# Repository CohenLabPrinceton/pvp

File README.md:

# The People's Ventilator Project

All information is in the documentation:
https://pvp.readthedocs.io/

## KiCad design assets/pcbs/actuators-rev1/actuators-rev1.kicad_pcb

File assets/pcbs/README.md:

# Content of pcbs
This folder contains PCB design files for the PVP1. There are two boards: one for the Actuators and one for the Sensors. They connect to the the Raspberry Pi 4 via 40-pin stackable headers. Uploaded as KiCad project files except where noted.

# Actuator Board (actuators-rev2)
	- Interfaces the Raspberry Pi to the inspiratory and expiratory valves through an array of solenoid drivers (ULN2003A Darlington transistor array)
	- Revision history:
		- rev2 (6/14/2020): Present version. Removed one screw terminal and the adjustable headers. Four of the darlington pairs are tied together to drive the expiratory valve, and three are tied together to drive the proportional valve. These connections are now permanent traces on the PCB.
		- rev1 (5/13/2020): Initial version. Three screw terminals intended to connect to valves. Included extra jumpers J4, J8, J9, and J10 designed to tie together Darlington pairs for felxibility if more current was needed to drive a particular valve.
		
# Sensor Board (pressure-rev2)
	- Interfaces four analog output sensors with the Raspberry Pi via I^2C commands to a 12-bit 4-channel ADC (Adafruit ADS1015)
	- Revision history:
		- rev2 (6/14/2020): Present version. Added a third auxiliary pressure sensor, and revised analog front-end for oxygen sensor. Added a TL7660 charge pump to provide a dual-sided supply to the INA126 instrumentation amplifier. Connections for I2C resistors removed.
		- rev1 (4/27/2020): Initial version. Shared as Gerber production files. Connections included for two pressure sensors, oxygen sensor, and flow sensor.

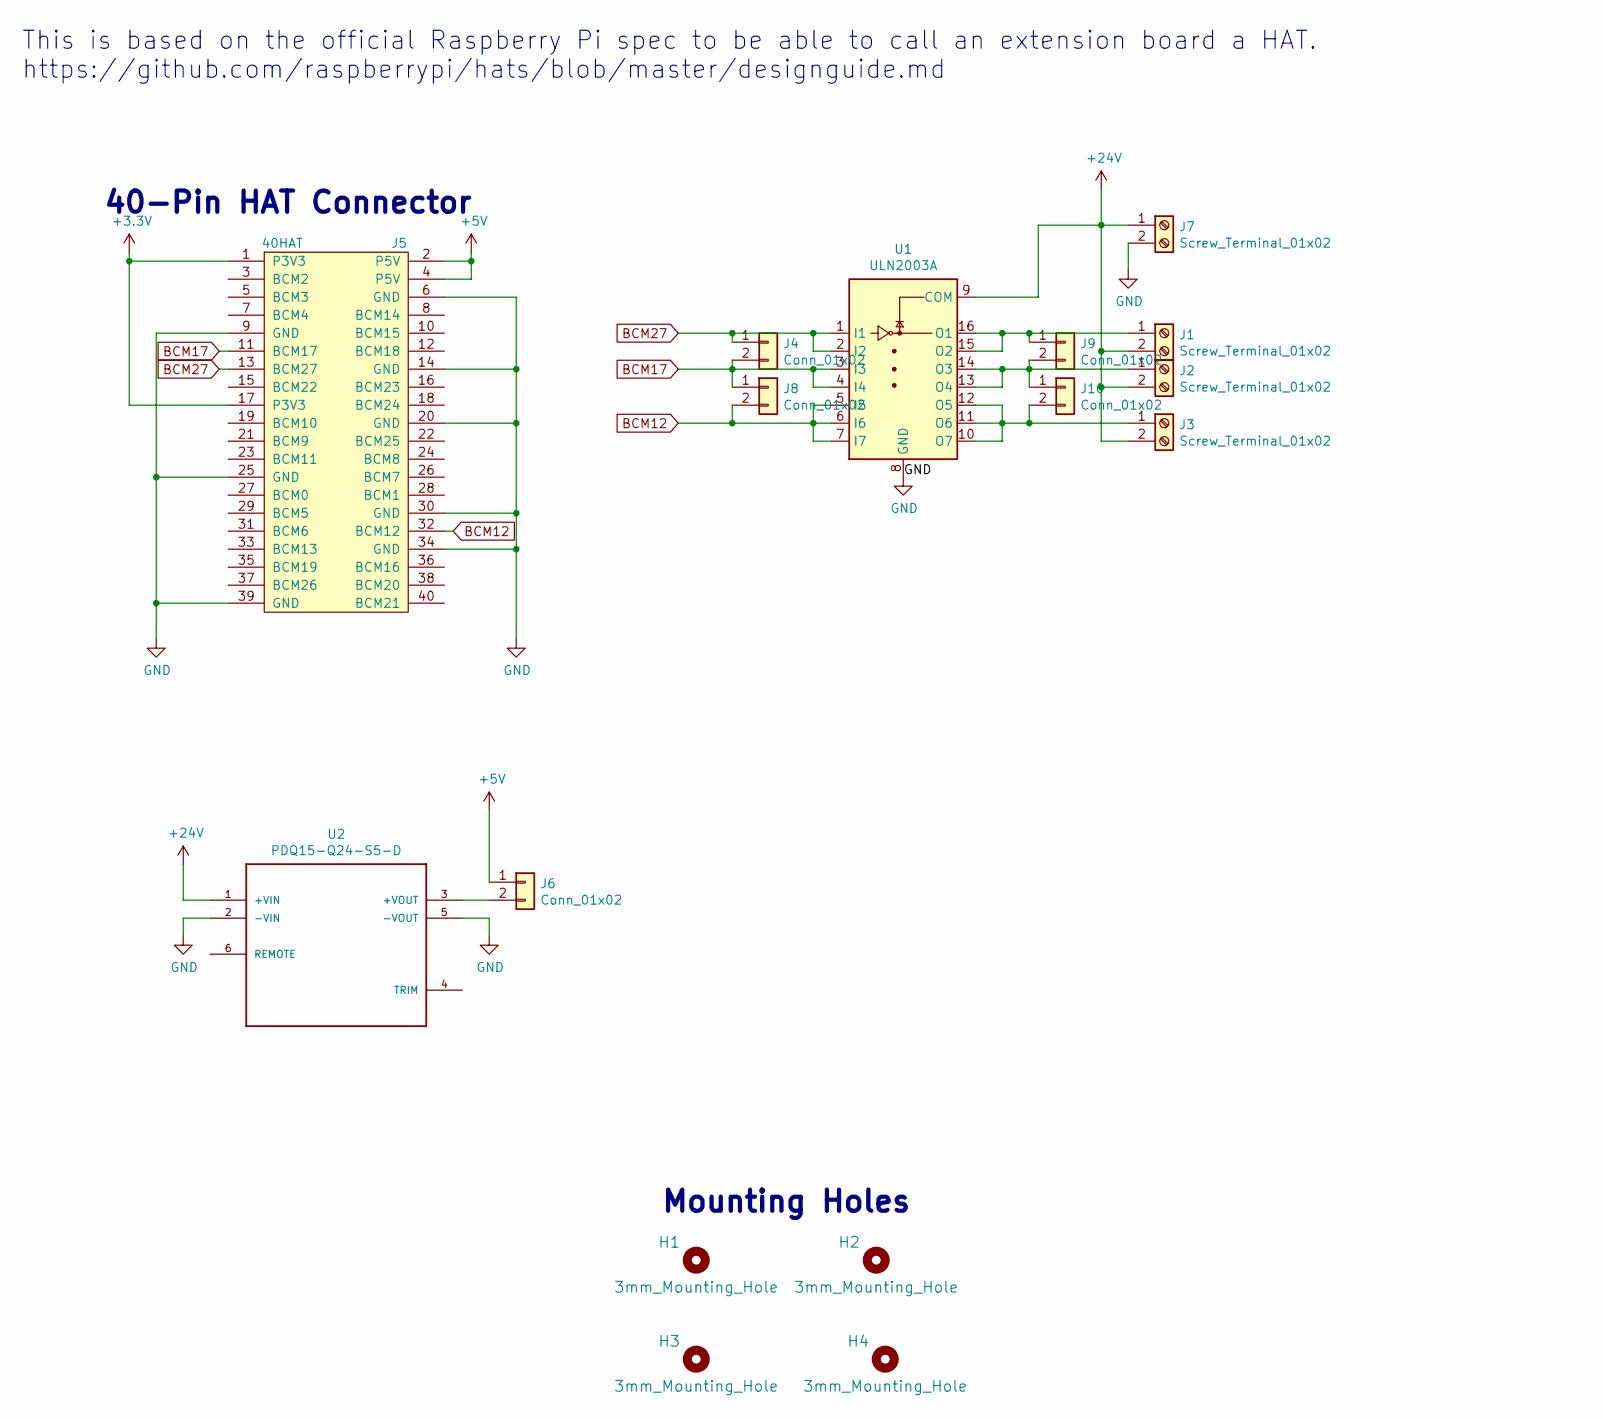
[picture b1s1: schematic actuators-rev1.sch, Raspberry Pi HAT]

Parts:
H1, H2, H3, H4: 3mm_Mounting_Hole; NPTH_3mm_ID
J1, J2, J3, J7: Screw_Terminal_01x02; TerminalBlock_Altech_AK300-2_P5.00mm
J4, J6, J8, J9, J10: Conn_01x02; PinHeader_1x02_P2.54mm_Vertical
J5: 40HAT; PinSocket_2x20_P2.54mm_Vertical
U1: ULN2003A; DIP-16_W7.62mm
U2: PDQ15-Q24-S5-D; CONV_PDQ15-Q24-S5-D

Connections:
+3V3: J5.1 (P3V3), J5.17 (P3V3)
+5V: J5.2 (P5V), J5.4 (P5V), J6.1
+24V: J1.2, J2.2, J3.2, J7.1, U1.9 (COM), U2.1 (+VIN)
BCM12: J5.32 (BCM12), J8.2, U1.5 (I5), U1.6 (I6), U1.7 (I7)
BCM17: J4.2, J5.11 (BCM17), J8.1, U1.3 (I3), U1.4 (I4)
BCM27: J4.1, J5.13 (BCM27), U1.1 (I1), U1.2 (I2)
GND: J5.6 (GND), J5.9 (GND), J5.14 (GND), J5.20 (GND), J5.25 (GND), J5.30 (GND), J5.34 (GND), J5.39 (GND), J7.2, U1.8 (GND), U2.2 (-VIN), U2.5 (-VOUT)
unnamed: J1.1, J9.1, U1.15 (O2), U1.16 (O1)
unnamed: J6.2, U2.3 (+VOUT)
unnamed: J2.1, J9.2, J10.1, U1.13 (O4), U1.14 (O3)
unnamed: J3.1, J10.2, U1.10 (O7), U1.11 (O6), U1.12 (O5)

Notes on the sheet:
Mounting Holes
40-Pin HAT Connector
This is based on the official Raspberry Pi spec to be able to call an extension board a HAT. https://github.com/raspberrypi/hats/blob/master/designguide.md

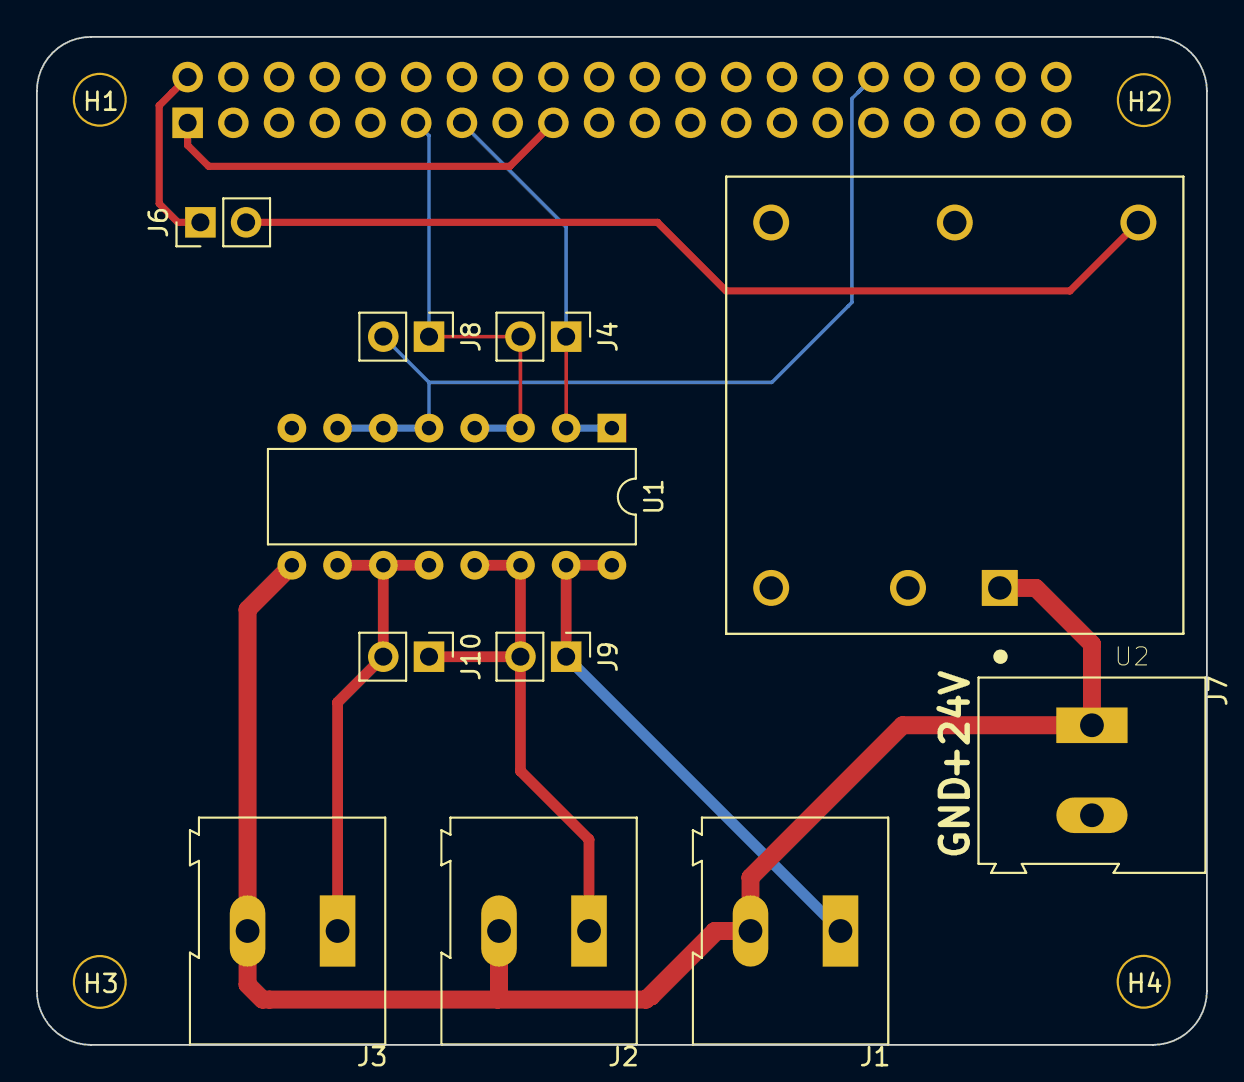
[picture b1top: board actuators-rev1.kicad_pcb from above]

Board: 4 copper layers, 65.0 x 56.0 mm, 16 parts (1 on the bottom side), 11 nets.

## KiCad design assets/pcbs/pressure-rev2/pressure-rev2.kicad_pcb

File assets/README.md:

# Content of assets
This folder contains all technical drawings for PVP1, the drawings for parts to be 3D-printed, and printed circuit boards.
In addition, to aid discoverability, we have generated a standardized Open Know How Manifest (OKH-manifest): [`okh-manifest.yml`](okh-manifest.yml). This follows the Open Know-How Manifest Specification Version 1.0. Finally, the file `PVP1 Assembly Instructions.pdf` contains detailed step-by-step assembly instructions.
The following folders exist:

# cad
Contains a 3D-printable PEEP valve, as single-use PEEP valves can be subject to supply chain limitations. 

# DXFs
Contains drawings for laser cutting of the chassis.

# PCBS
This folder contains all of the electrical design files for our custom PCBs. 

# SOLIDWORKS
This folder contains CAD drawings of PVP1, more specifically:
1. Technical drawings of the PVP1 Mk3, in Solidworks. This is the device documented in the article, and featured in the detailed assembly instructions. This final version of PVP1 removed non-critical components, such as the humidifier and Gauges, and introduced more standardized parts.
1. The previous version of the device, Mk2, using few standardized components, and featuring a humidifier. Notice the `CPAP_BIPAP_HEATER_HUMIDIFIER_ASSY`.
1. Mk1, the first version of PVP1. This served as an early sketch about what to include in the design

# STLs
This folder contains all of our 3D printed components/fixtures that are not included in our Bill-of-Materials.

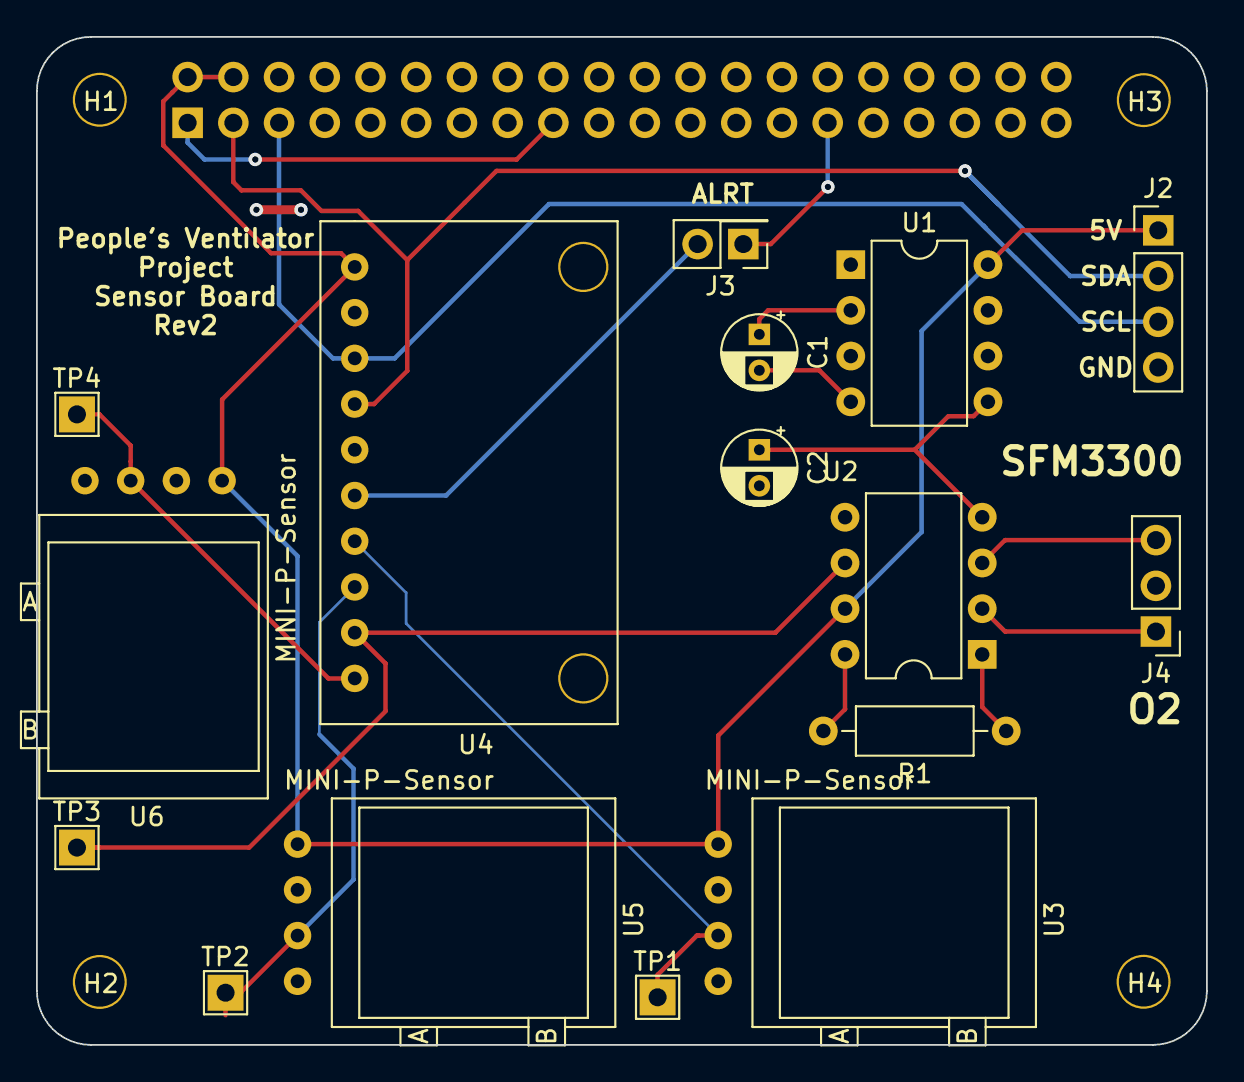
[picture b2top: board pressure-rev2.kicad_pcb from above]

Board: 2 copper layers, 65.0 x 56.0 mm, 21 parts (1 on the bottom side), 18 nets.

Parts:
C1, C2: CP1; CP_Radial_D4.0mm_P2.00mm
H1, H2, H3, H4: 3mm_Mounting_Hole; NPTH_3mm_ID
J1: 40HAT; PinSocket_2x20_P2.54mm_Vertical
J2: Conn_01x04; PinHeader_1x04_P2.54mm_Vertical
J3: Conn_02x01; PinHeader_2x01_P2.54mm_Vertical
J4: Conn_01x03; PinHeader_1x03_P2.54mm_Vertical
R1: R; R_Axial_DIN0207_L6.3mm_D2.5mm_P10.16mm_Horizontal
TP1, TP2, TP3, TP4: TestPoint; TestPoint_THTPad_2.0x2.0mm_Drill1.0mm
U1: TL7660; DIP-8_W7.62mm
U2: INA126; DIP-8_W7.62mm
U3, U5, U6: MINI-P-Sensor; MINI-P-Sensor-Horizontal
U4: Adafruit_ADS1115

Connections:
+3V3: J1.1, J1.17
+5V: J1.2, J1.4, J2.1, U1.8, U2.7, U3.1, U4.1, U5.1, U6.1
/J_ALRT: J1.29, J3.1
/SCL: J1.5, J2.3, U4.3
/SDA: J1.3, J2.2, U4.4
GND: C2.2, J1.6, J1.9, J1.14, J1.20, J1.25, J1.30, J1.34, J1.39, J2.4, J4.2, U1.3, U2.5, U3.2, U4.2, U4.5, U5.2, U6.2
unnamed: C1.1, U1.2
unnamed: C1.2, U1.4
unnamed: C2.1, U1.5, U2.4
unnamed: J3.2, U4.6
unnamed: J4.1, U2.2
unnamed: J4.3, U2.3
unnamed: R1.1, U2.1
unnamed: R1.2, U2.8
unnamed: TP1.1, U3.3, U4.7
unnamed: TP2.1, U4.8, U5.3
unnamed: TP3.1, U2.6, U4.9
unnamed: TP4.1, U4.10, U6.3

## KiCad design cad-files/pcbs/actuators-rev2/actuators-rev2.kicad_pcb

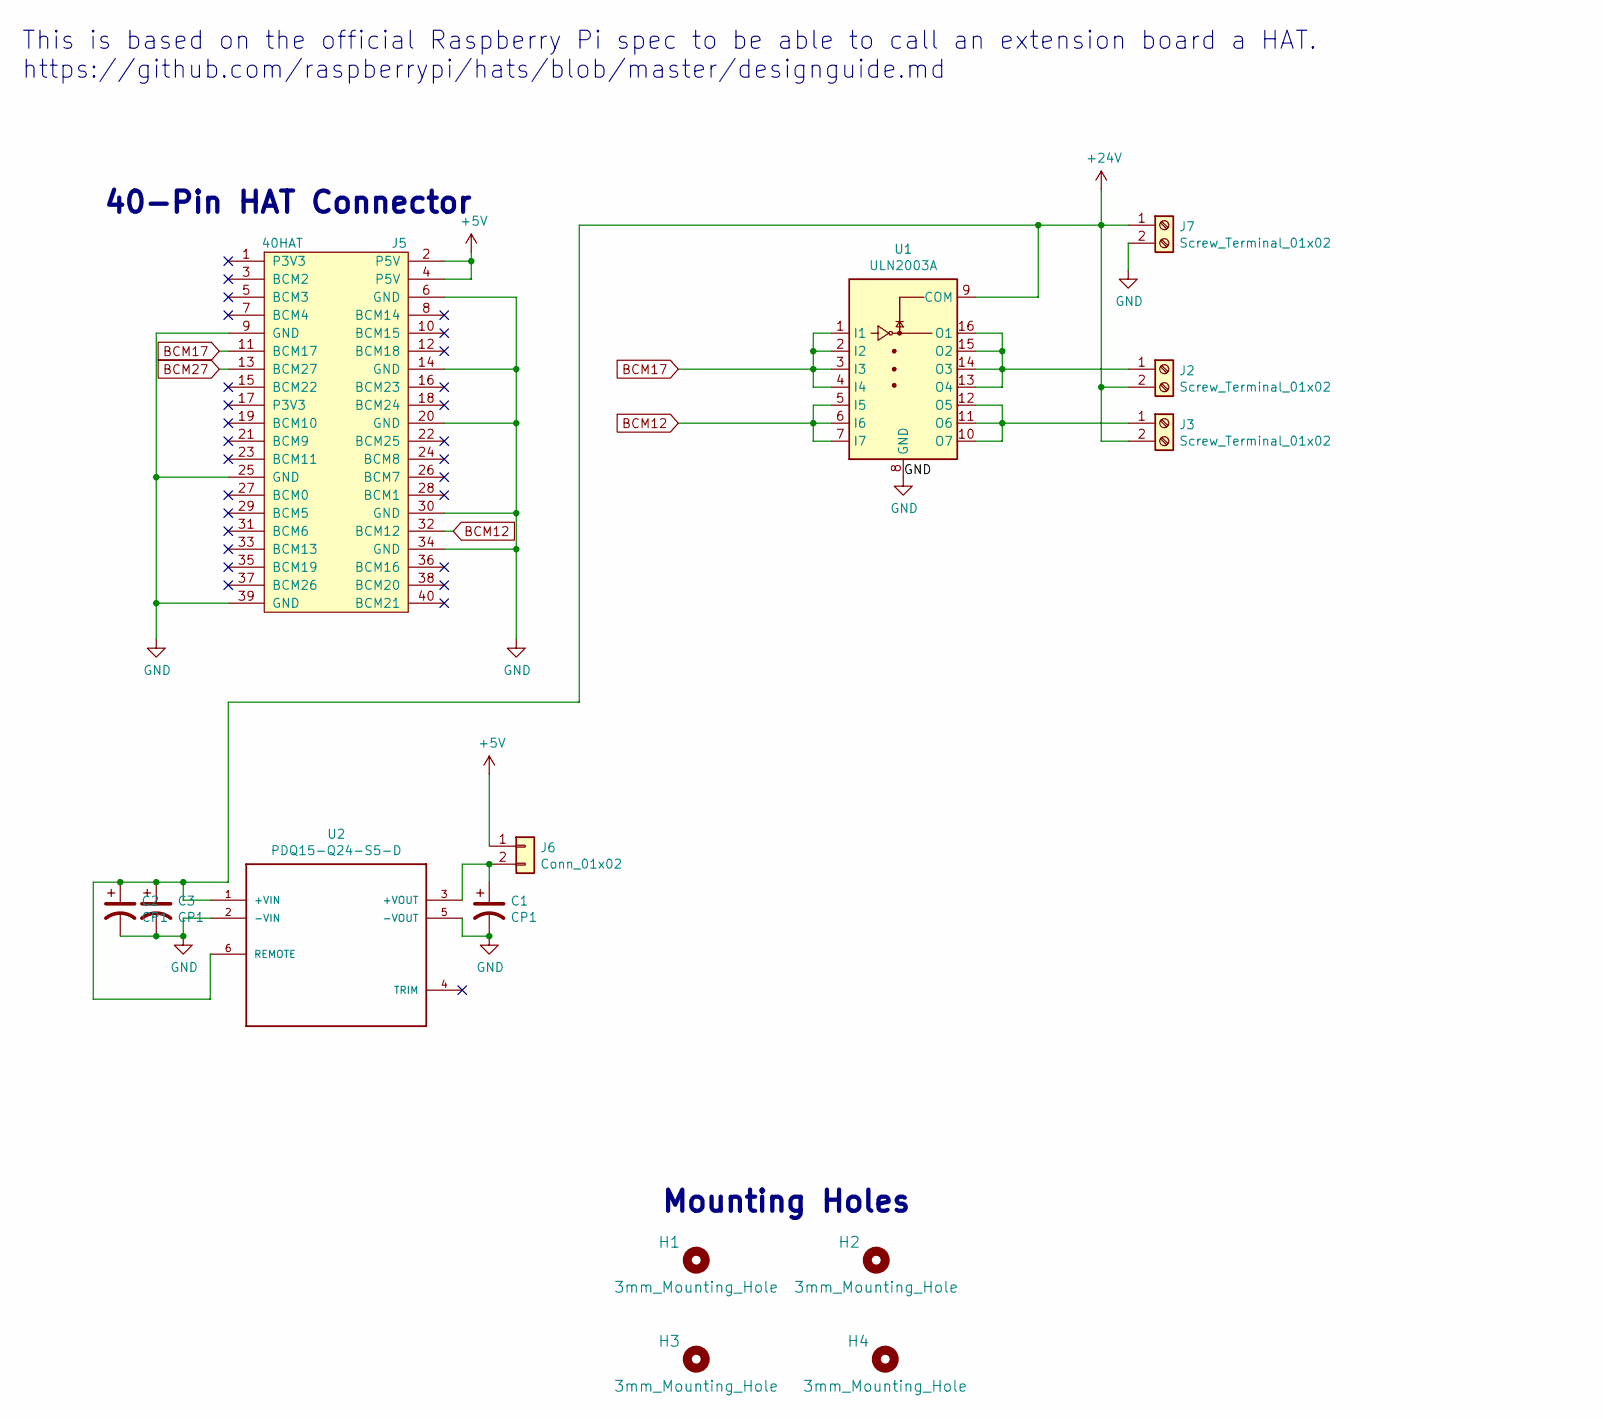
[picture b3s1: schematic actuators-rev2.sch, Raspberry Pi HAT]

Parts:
C1: CP1; CP_Radial_D5.0mm_P2.00mm
C2, C3: CP1; CP_Radial_D5.0mm_P2.50mm
H1, H2, H3, H4: 3mm_Mounting_Hole; NPTH_3mm_ID
J2, J3, J7: Screw_Terminal_01x02; TerminalBlock_Altech_AK300-2_P5.00mm
J5: 40HAT; PinSocket_2x20_P2.54mm_Vertical
J6: Conn_01x02; PinHeader_1x02_P2.54mm_Vertical
U1: ULN2003A; DIP-16_W7.62mm
U2: PDQ15-Q24-S5-D; CONV_PDQ15-Q24-S5-D

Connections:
+5V: J5.2 (P5V), J5.4 (P5V), J6.1
+24V: C2.1, C3.1, J2.2, J3.2, J7.1, U1.9 (COM), U2.1 (+VIN), U2.6 (REMOTE)
BCM12: J5.32 (BCM12), U1.5 (I5), U1.6 (I6), U1.7 (I7)
BCM17: J5.11 (BCM17), U1.1 (I1), U1.2 (I2), U1.3 (I3), U1.4 (I4)
BCM27: J5.13 (BCM27)
GND: C1.2, C2.2, C3.2, J5.6 (GND), J5.9 (GND), J5.14 (GND), J5.20 (GND), J5.25 (GND), J5.30 (GND), J5.34 (GND), J5.39 (GND), J7.2, U1.8 (GND), U2.2 (-VIN), U2.5 (-VOUT)
unnamed: C1.1, J6.2, U2.3 (+VOUT)
unnamed: J2.1, U1.13 (O4), U1.14 (O3), U1.15 (O2), U1.16 (O1)
unnamed: J3.1, U1.10 (O7), U1.11 (O6), U1.12 (O5)

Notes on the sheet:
Mounting Holes
40-Pin HAT Connector
This is based on the official Raspberry Pi spec to be able to call an extension board a HAT. https://github.com/raspberrypi/hats/blob/master/designguide.md

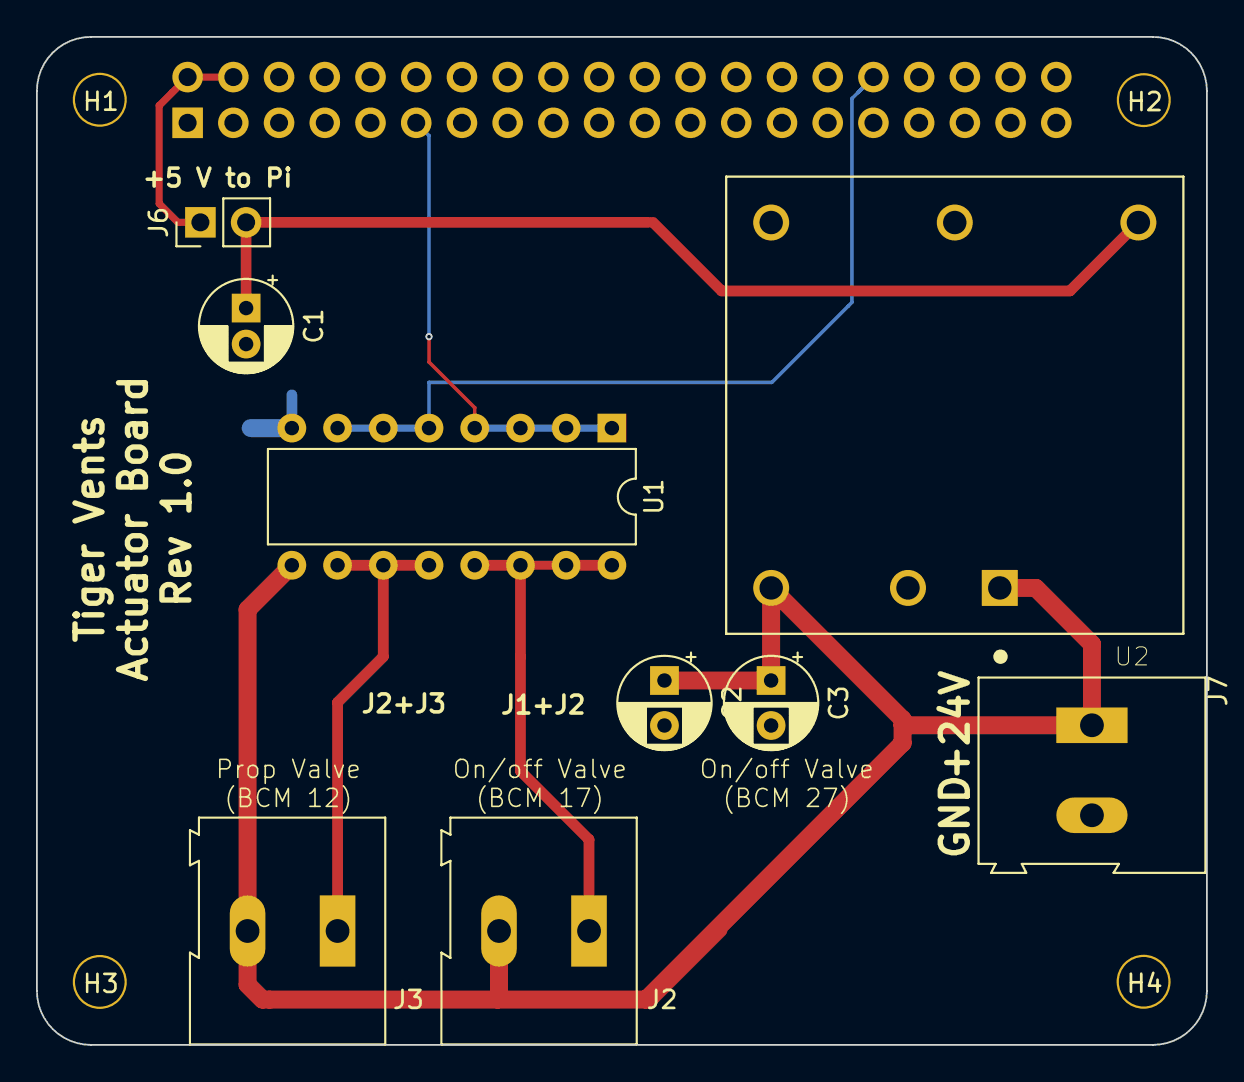
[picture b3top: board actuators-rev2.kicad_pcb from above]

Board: 4 copper layers, 65.0 x 56.0 mm, 14 parts (1 on the bottom side), 8 nets.

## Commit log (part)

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2020-08-11 Update test_timeoutdecorator.py
    This should be consistent as 5*dt
2020-08-11 ignoring build and dist
2020-08-12 audio system using QSoundEffect for buffering
2020-08-12 maybe docker wasnt the right idea
2020-08-12 refactoring vent to pvp
    and updating some missing entries in the docs and rebuilding the docs
2020-08-12 moving some external files to a subdirectory in pvp for packaging
2020-08-12 working on tests -- just wanna look at coverage report to see what's missing
2020-08-12 working on some code coverage of main gui widget
2020-08-12 coordinator doesn't kill controller on stop...
2020-08-12 killing dead code
    - RIP the ideal waveform plot it was a good idea ahead of its time.
    - RIP the rangeslider which should be built into Qt but we had to do hand to hand fucking pixelwise drawing for like a week to make. it still was sorta shitty so good riddance
    - Welcome back to life tests for doubleslider
2020-08-12 always do coveralls!!
2020-08-12 Checking in GUI tests and some healthy code cleanup (#135)
    * working on tests -- just wanna look at coverage report to see what's missing
    * coveralls always!
    * working on some code coverage of main gui widget
    * coordinator doesn't kill controller on stop...
    * we got too soft on em, actually killing when closing gui
    also explicitly testing VTE since its just a lil different as it doesnt have a corresponding control in the controller
2020-08-13 little touchups for screenshot
    fix misnamed valve reset function in main
2020-08-14 updating badge urls
2020-08-14 hook up mute button
    - add FIO2 to available plots
    - controller resets _last_update time when starting so don't reset cycle immediately on start
    - version indicator to control panel
    - labels off of plot controls
    - made limit labels clearer in plots
    - added logo to gui
2020-08-14 change colors of display objects when they cause alarms
    - add 'cause' field to alarm objects
    - add 'depends' and 'value_names' to alarm rules to make it easier for them to be queried
2020-08-14 keep color coding consistent through state changes update screenshot to use color coding
2020-08-14 updating link to docs
2020-08-14 refactoring into assets directory
2020-08-15 prevent erroring
2020-08-15 quieter pylint
2020-08-15 actually including iamges
2020-08-15 test flexbox, add placeholders, basic toctree shifting
2020-08-15 favicon remove image logo
2020-08-15 on second thought that was a bad organization
2020-08-15 correct image url
2020-08-15 header text, icon size,
2020-08-15 hideen homepage toctrees
2020-08-15 doubt this toctree works
2020-08-15 actually add the depends
2020-08-15 git repo
2020-08-15 actually in a directive
2020-08-15 relative path?
2020-08-15 header margins
2020-08-15 min_width
2020-08-15 sizing and wrapping
2020-08-15 whoops forgot how sass worked lol
2020-08-15 styling subelements
2020-08-15 wait wat
2020-08-15 idk just smag it
2020-08-15 has the output been wrong this whole time?
2020-08-15 basic software copy
2020-08-15 css grid
2020-08-16 fixing links
2020-08-16 testing bolded links, adding contributing stub
2020-08-16 reordering Software Toctree
2020-08-16 software overview, clickable this time
2020-08-16 include libpulse-dev
2020-08-16 mock import
2020-08-16 expanding gui to multiple pages refactoring Vent_GUI to PVP_Gui
2020-08-16 splitting widgets out to different pages, adding gui overview
2020-08-16 bigger class size name
2020-08-16 initial gui docs
2020-08-16 unnest toctree
2020-08-16 take out unnecessary header
2020-08-16 good ole fashioned way of collapsing
2020-08-16 docs for main gui widget software overview
2020-08-16 do class level docstrings render better?
2020-08-16 Pull and squash initial docs styling and GUI documentation (#138)
    * test pylint
    * prevent erroring
    * quieter pylint
    * test images, include summary report
    * actually including iamges
    * test flexbox, add placeholders, basic toctree shifting
2020-08-16 added basic copy from paper to intro
2020-08-16 added electronics diagram
2020-08-16 added some writeup of pvp electronics/hardware
2020-08-16 common module overview
2020-08-16 Docstrings for values.py
2020-08-17 splitting alarm into multiple files
2020-08-17 actually adding to toctree
2020-08-17 test syntax highlighting?
2020-08-17 finding the right objects maybe?
2020-08-17 moving example to alarm rule page
    adding docstring to alarm definition
2020-08-17 toc in the main page
2020-08-17 correct titles in alarm toc
2020-08-17 link to alarm rule source
2020-08-17 alarm manager documentation
2020-08-17 condition documentation
2020-08-17 importing correctly
2020-08-17 prefs documentation
2020-08-17 messages docs
2020-08-17 test order of class and init docstrings
2020-08-17 unit conversions docs
2020-08-18 alarm bar documentation
2020-08-18 source link color
2020-08-18 control panel docs
2020-08-18 plot docs
2020-08-18 statement on components
2020-08-18 Jonny finished with docs (#139)
    whup whup
    - narrative documentation for software overview, all gui modules, all alarm modules, common.values , common.message (except for stuff manuel needs ta do), common.loggers (except for stuff manuel need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
    - API documentation, docstrings for every method, user-facing attribute, function and constant in all the above. Only exception is gui.widgets.components which are p self explanatory
    - Figures for software overview, gui overview, gui screenshot
    - cleaned up dead/obsolete code with no uses in all the above
    * common module overview
2020-08-18 testing dependencies
2020-08-18 alarm severity condition
2020-08-18 unit conversion tests lol
2020-08-18 sorta weak conversion test but it is specific enough that it works for now
2020-08-18 alarm bar test
2020-08-18 resetting alarm manager state
2020-08-18 dont include the screenshot function...
2020-08-18 shorten delays
2020-08-18 Uploading STL files 8/18/20
2020-08-18 test breath detection
2020-08-18 test timer in ms
2020-08-18 correct message in confirm unsafe
2020-08-18 test unit conversions in run
2020-08-18 stop the timers
2020-08-18 test plot toggling
2020-08-19 correct unit conversions, and unit conversions in control tests
2020-08-19 fix heartbeat call to setText
2020-08-19 oh and updating the unit conversion test
    doing a round instead of int which i assume takes floor
2020-08-19 mercifully shorten testing time by skipping pointless tests
2020-08-19 testing keyboard actions on editable label separately from general control testing
2020-08-19 Gui tests (#140)
    Tests for all my shit.
    also
    - some improvements on adding conditions together (copying the object rather than modifying in place)
    - adding reset to condition addition
    - fixing a disastrously incorrect unit conversion
    - get_breath_detection method for controller since we decided against having a generalized messaging infrastructure and this is the consequence!
2020-08-19 generated gerber files
2020-08-19 more pcb docs
2020-08-19 added sensor pcb bom
2020-08-19 list edits
2020-08-19 try bom path
2020-08-19 upres schematics
2020-08-19 Update hardware_electronics.rst
    spacing for figure captions
2020-08-19 Update hardware_electronics.rst
    spacing between toctree option block
2020-08-19 Update hardware_electronics.rst
    maybe relative links work?
2020-08-19 Update hardware_electronics.rst
    trying two ways -- url and with the full relative path (from conf.py)
2020-08-19 update sensor bom
2020-08-19 enum lists?
2020-08-20 sizing
2020-08-20 edit powerio bom
2020-08-20 figwidth
2020-08-20 remove toctree
2020-08-21 terminate a tag correctly
2020-08-21 cleaning up some hardware docs
2020-08-24 fix cap error in bom
2020-08-24 cleaning up docs
2020-08-24 update schematic img and file for sensor board
2020-08-24 lots of hardware docs reconfiguring
2020-08-24 hardware docs reconfiguration
2020-08-24 add a toc
2020-08-24 tocs, tocs everywhere
2020-08-24 organizing the tocs
2020-08-24 added performance page
2020-08-24 trying to fix the toc
2020-08-24 add pcb project links
2020-08-24 get the assembly on track
2020-08-25 add figures and performance writeup
2020-08-25 update performance
2020-08-26 performance update
2020-08-26 few text updates
2020-08-26 making controller more robust
2020-09-03 local changes for the long run
2020-09-03 removed default PIP in HAPA, as discussed
2020-09-04 updated sensor pcb schematic to reflect pressure/airflow sensor swap
2020-09-04 New tests for the logger
2020-09-05 bug
    no pylab needed in the tests
2020-09-05 few more outputs, and a MockHAL
    ...if HAL doesn't load. Fixed timeout 5 seconds
2020-09-05 too many outputs for travis to handle :-)
2020-09-06 try without these two tests
2020-09-06 one more test
2020-09-06 come on travis; you can do it
2020-09-06 streamlined hal test
2020-09-06 more cleanup
2020-09-06 nan pressure test
2020-09-06 fix travis?
2020-09-06 new nantest
2020-09-06 update for travis
2020-09-06 getting rid of unused code
2020-09-06 removed tre/except and replaced with ifs
2020-09-06 whoopsi
2020-09-07 Cover HAPA and TECHA
    and ignore the OS tests for running out of space
2020-09-07 final check: the no-alarm case should return none
2020-09-07 just a stub, can be removed from travis
2020-09-08 some more cleanup
2020-09-08 added missing tests of /loggers.py
2020-09-23 changed battery fig, with readjusted voltage offset for flow sensor
2020-10-02 added project bom
2020-10-02 added disclaimer
2020-10-02 controller description
2020-10-02 fix typos in disclaimer
2020-10-05 Added link to Solidworks assembly drive
2020-10-06 added funding to main page
2020-10-06 Typos
2020-10-06 Delete LEFT_SCREEN_MODULE_MOUNT.STL
    Outdated mounting strategy
2020-10-06 Delete RIGHT_SCREEN_MODULE_MOUNT.STL
    Outdated mounting strategy
2020-10-06 Added Trevor Day School acknowl.
2020-10-06 Markdown typo
2020-10-06 Added pigpio latency
2020-10-06 Added note about Advanced Circuits
2020-10-06 Moved text location
2020-10-08 cleanup stale docs
2020-10-09 cleanup + oxygen-redout in /pref.py
    As the summary says: Cleanup + Oxygen-readout in /prefs.py
2020-10-09 Update to version 0.3.0
    as summarized; see __init__
2020-10-09 more text for controller
2020-10-09 removed thee ipynb checkpoints
2020-10-09 and updates for folder structure
2020-10-09 that should cover another previously untested line
    ...in coordinator line 144
2020-10-09 more tests for common
    ...a few more lines tested now.
    Also __members__ doesn't exit
2020-10-09 last missing test for ControlSetting
2020-10-10 removed assert + last missing tests on message.py
    ...as description says
2020-10-10 deleted unused code + another coordinator test
2020-10-11 Update to test_io_sensors...
    ...to check DLite. Also cleanup of io
2020-10-12 refactoring main.py + new tests for main.py
    Also some cleanup in control_module, and new HALMock-Class: same internal variables as hal, but no pigpio dependency.
2020-10-12 SImplify tests on main
    and allows to run pvp.main.main(['--simulation']) as well as main(sys.argv[1:])
2020-10-15 Updated STLs
2020-10-15 Moved image placement
2020-10-18 add tests
2020-10-19 Edits as discussed
    (1) Assertions are back in `message.py`
    (2) pytest-code was moved to /tests. Is not needed anymore in messages.py
2020-10-19 typo; that should have been in the line above
2020-10-19 cleanup of the controller
2020-10-19 cleanup; didn't mean to push the logs...
2020-11-06 Delete dinky-devices.ini
    Unused and confusing
2021-01-07 Update GPIO pin for expiratory valve
    Match latest Rev 1.0 board and RTD
2021-12-22 restructuring docs to be nested instead of flat...
2021-12-22 use a .rtd.yaml file instead
2021-12-22 version specified separately in travis, swap recommonmark for myst
2021-12-22 split requirements into requirements_tests, moved out of .travis.yml version specifier for pytest-qt
2021-12-22 install package
2021-12-22 headers in assembly instructions
2022-01-17 Version 1
2022-01-19 updates to docs with links to SolidWorks / pdf instructions
2022-01-24 some cleanup
2022-01-26 Adding a "no cover" to coordinator's "stop" method
    ... as this just runs into a `...pass`
2022-01-27 fixing docs - limit pyqtgraph version with ~= instead of >= in requirements_docs.txt - remove /docs, rename /_docs to /docs
2022-01-27 setuptools packaging hurting my soul
2022-01-27 [skip travis] debugging docs and internal links
2022-01-27 [skip travis] PySide2<5.14 not compatible with python >=3.8
2022-01-27 [skip travis] Fixing links and table widths
2022-01-27 Fourth column breaks setting explicit widths, but removing that for now
2022-01-31 Update to readme
    with our zenodo doi
